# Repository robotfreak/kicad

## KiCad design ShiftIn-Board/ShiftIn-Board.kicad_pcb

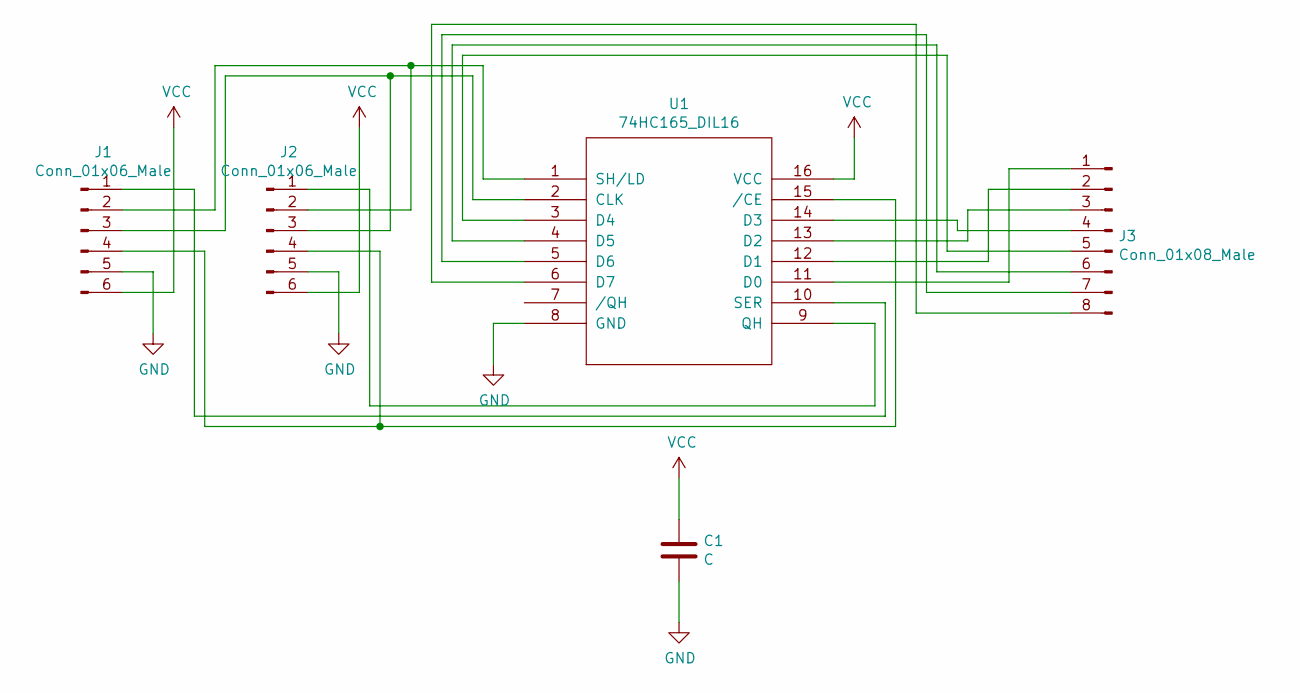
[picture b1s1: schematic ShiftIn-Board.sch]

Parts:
C1: C; C_1206_3216Metric
J1, J2: Conn_01x06_Male; PinHeader_1x06_P2.54mm_Vertical
J3: Conn_01x08_Male; PinHeader_1x08_P2.54mm_Vertical
U1: 74HC165_DIL16; SOIC-16_3.9x9.9mm_P1.27mm

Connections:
GND: C1.2, J1.5, J2.5, U1.8 (GND)
unnamed: J1.1, U1.10 (SER)
unnamed: J1.2, J2.2, U1.1 (SH/LD)
unnamed: J1.3, J2.3, U1.2 (CLK)
unnamed: J1.4, J2.4, U1.15 (/CE)
unnamed: J2.1, U1.9 (QH)
unnamed: J3.1, U1.11 (D0)
unnamed: J3.2, U1.12 (D1)
unnamed: J3.3, U1.13 (D2)
unnamed: J3.4, U1.14 (D3)
unnamed: J3.5, U1.3 (D4)
unnamed: J3.6, U1.4 (D5)
unnamed: J3.7, U1.5 (D6)
unnamed: J3.8, U1.6 (D7)
VCC: C1.1, J1.6, J2.6, U1.16 (VCC)

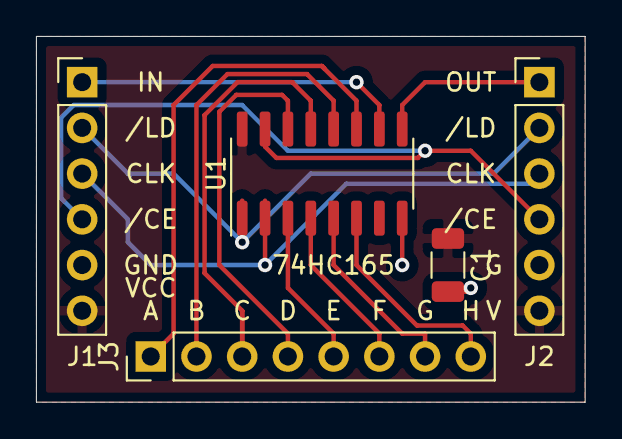
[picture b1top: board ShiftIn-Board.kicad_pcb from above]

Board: 2 copper layers, 30.5 x 20.3 mm, 5 parts (0 on the bottom side), 15 nets.

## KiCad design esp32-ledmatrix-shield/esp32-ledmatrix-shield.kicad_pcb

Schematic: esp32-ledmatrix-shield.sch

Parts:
C1: CP; CP_Radial_D10.0mm_P5.00mm_P7.50mm
J1: Power; BarrelJack_Horizontal
J2: Power; TerminalBlock_Phoenix_MKDS-3-4-5.08_1x04_P5.08mm_Horizontal
J3: JIN; PinSocket_2x08_P2.54mm_Vertical
J4: Buzzer; PinHeader_1x03_P2.54mm_Vertical
J5: Ctrl2; PinHeader_1x04_P2.54mm_Vertical
J6, J16: VIN ext; PinHeader_1x02_P2.54mm_Vertical
J7: Power; PinHeader_1x02_P2.54mm_Vertical
J8: C; SolderJumper-3_P1.3mm_Open_Pad1.0x1.5mm
J9: D; SolderJumper-3_P1.3mm_Open_Pad1.0x1.5mm
J10: Ctrl1; PinHeader_1x04_P2.54mm_Vertical
J11: E; SolderJumper-3_P1.3mm_Open_Pad1.0x1.5mm
J12, J13, J14: I2C; PinHeader_1x04_P2.54mm_Vertical
J15: JOUT; PinHeader_2x08_P2.54mm_Vertical
JP1, JP2, JP3, JP4: Jumper; SolderJumper-2_P1.3mm_Open_Pad1.0x1.5mm
R1, R2, R3, R4: 4k7; R_1206_3216Metric
U1: ESP32NODEMCU; ESP32-DIP-38_1000_ELL

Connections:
+3V3: J5.2, J10.2, J12.2, J13.2, J14.2, JP4.2, R1.1, R2.1, R3.1, R4.1, U1.1 (3V3)
+5V: J16.1
+5VA: C1.1, J1.1, J2.1, J2.2, J4.3, J6.1, J7.1
/A: J3.9, U1.31 (GPIO19)
/B: J3.10, U1.37 (GPIO23)
/B1: J3.3, J15.6
/B2: J3.7, J15.3
/C: J3.11, J8.2
/C': J8.3, U1.30 (GPIO18)
/CLK: J3.13, U1.12 (GPIO14)
/D: J3.12, J9.2
/E: J3.8, J11.2
/G1: J3.2, J15.5
/G2: J3.6, J15.2
/LAT: J3.14, U1.7 (GPIO32)
/OE: J3.15, U1.11 (GPIO27)
/R1: J3.1, U1.10 (GPIO26)
/R2: J3.5, J15.1
/SCL: J5.4, J12.4, J13.4, J14.4, R3.2, U1.36 (GPIO22)
/SCL2: J10.4, R1.2, U1.27 (GPIO16)
/SDA: J5.3, J12.3, J13.3, J14.3, R4.2, U1.33 (GPIO21)
/SDA2: J10.3, R2.2, U1.26 (GPIO4)
GND: C1.2, J1.2, J1.3, J2.3, J2.4, J3.4, J3.16, J4.1, J5.1, J7.2, J8.1, J9.1, J10.1, J11.1, J12.1, J13.1, J14.1, JP1.1, JP2.1, JP3.2, U1.38 (GND)
unnamed: J4.2, U1.13 (GPIO12)
unnamed: J6.2, U1.19 (VIN)
unnamed: J9.3, U1.29 (GPIO5)
unnamed: J11.3, U1.28 (GPIO17)
unnamed: J16.2, U1.16 (GPIO9)
unnamed: JP1.2, U1.14 (GND)
unnamed: JP2.2, U1.15 (GPIO13)
unnamed: JP3.1, U1.24 (GPIO2)
unnamed: JP4.1, U1.23 (GPIO15)

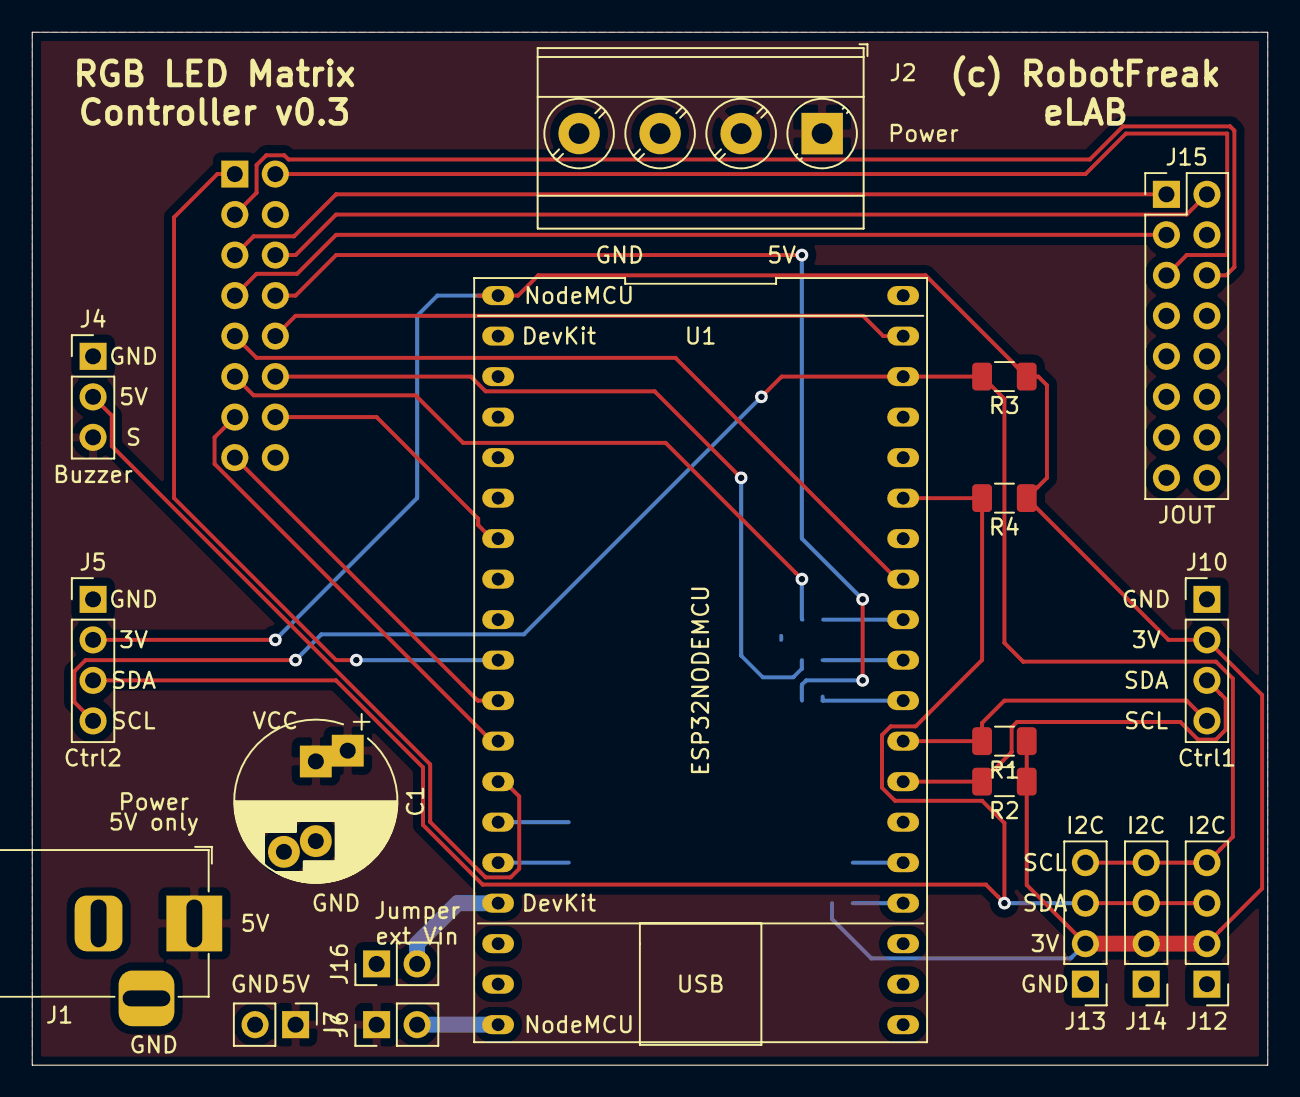
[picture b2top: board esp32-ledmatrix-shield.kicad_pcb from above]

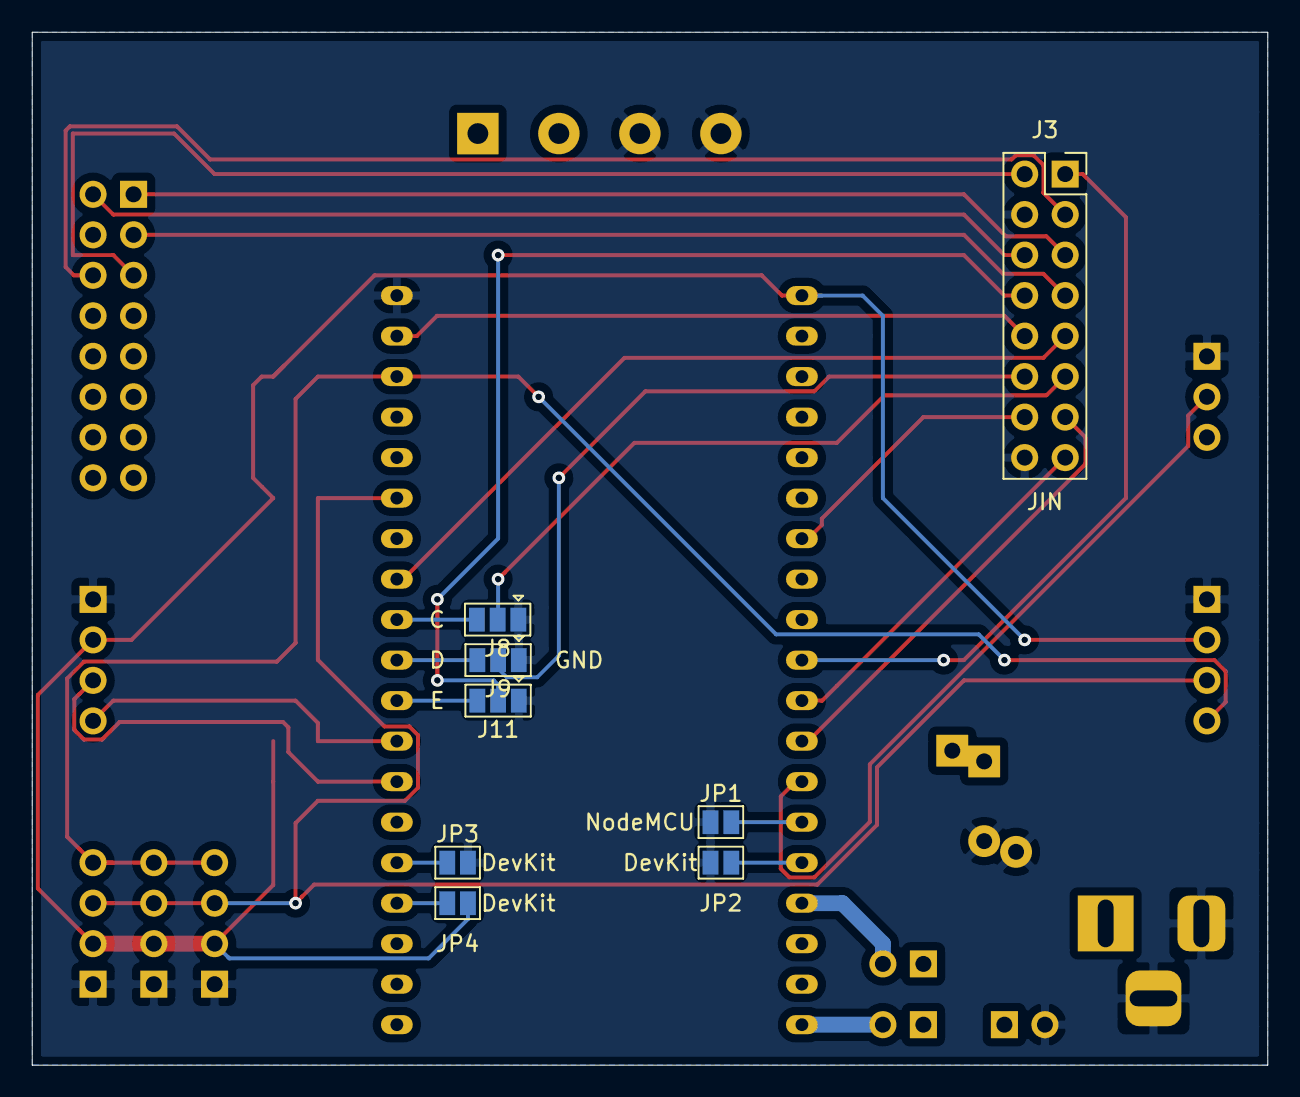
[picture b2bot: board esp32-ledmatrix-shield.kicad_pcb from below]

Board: 2 copper layers, 77.5 x 64.8 mm, 26 parts (8 on the bottom side), 31 nets.

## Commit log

2019-10-25 added esp32 ledmatrix shield
2019-11-22 schematic and pcb v0.3 devkit support
2019-12-07 added lib _sch
2019-12-08 added cache and rescue lib
2020-10-08 added ShiftIn-Board v0.1
2020-10-08 Shiftin-Board v0.2
